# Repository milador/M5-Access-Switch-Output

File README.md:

# M5-Access-Switch-Output

A Wi-Fi enabled Adaptive Switch Output device based on ESP32 M5StickC/M5StickCPlus which offers up to two 3.5mm switch outputs. The M5 Switch Output can be used to operate up to two switch adapted devices.

## Requirements and setup instructions 
The setup process is divided to three main catagories:

  1. [Hardware](./Hardware/) : The required hardware and design files
  2. [Software](./Software/) : The required software
  3. [Documentation](./Documentation/) : The assembly guide,user guide and other documents 

## License

### MIT License

Copyright (c) 2022 milador

Permission is hereby granted, free of charge, to any person obtaining a copy of this software and associated documentation files (the "Software"), to deal in the Software without restriction, including without limitation the rights to use, copy, modify, merge, publish, distribute, sublicense, and/or sell copies of the Software, and to permit persons to whom the Software is furnished to do so, subject to the following conditions:

The above copyright notice and this permission notice shall be included in all copies or substantial portions of the Software.

THE SOFTWARE IS PROVIDED "AS IS", WITHOUT WARRANTY OF ANY KIND, EXPRESS OR IMPLIED, INCLUDING BUT NOT LIMITED TO THE WARRANTIES OF MERCHANTABILITY, FITNESS FOR A PARTICULAR PURPOSE AND NONINFRINGEMENT. IN NO EVENT SHALL THE AUTHORS OR COPYRIGHT HOLDERS BE LIABLE FOR ANY CLAIM, DAMAGES OR OTHER LIABILITY, WHETHER IN AN ACTION OF CONTRACT, TORT OR OTHERWISE, ARISING FROM, OUT OF OR IN CONNECTION WITH THE SOFTWARE OR THE USE OR OTHER DEALINGS IN THE SOFTWARE.

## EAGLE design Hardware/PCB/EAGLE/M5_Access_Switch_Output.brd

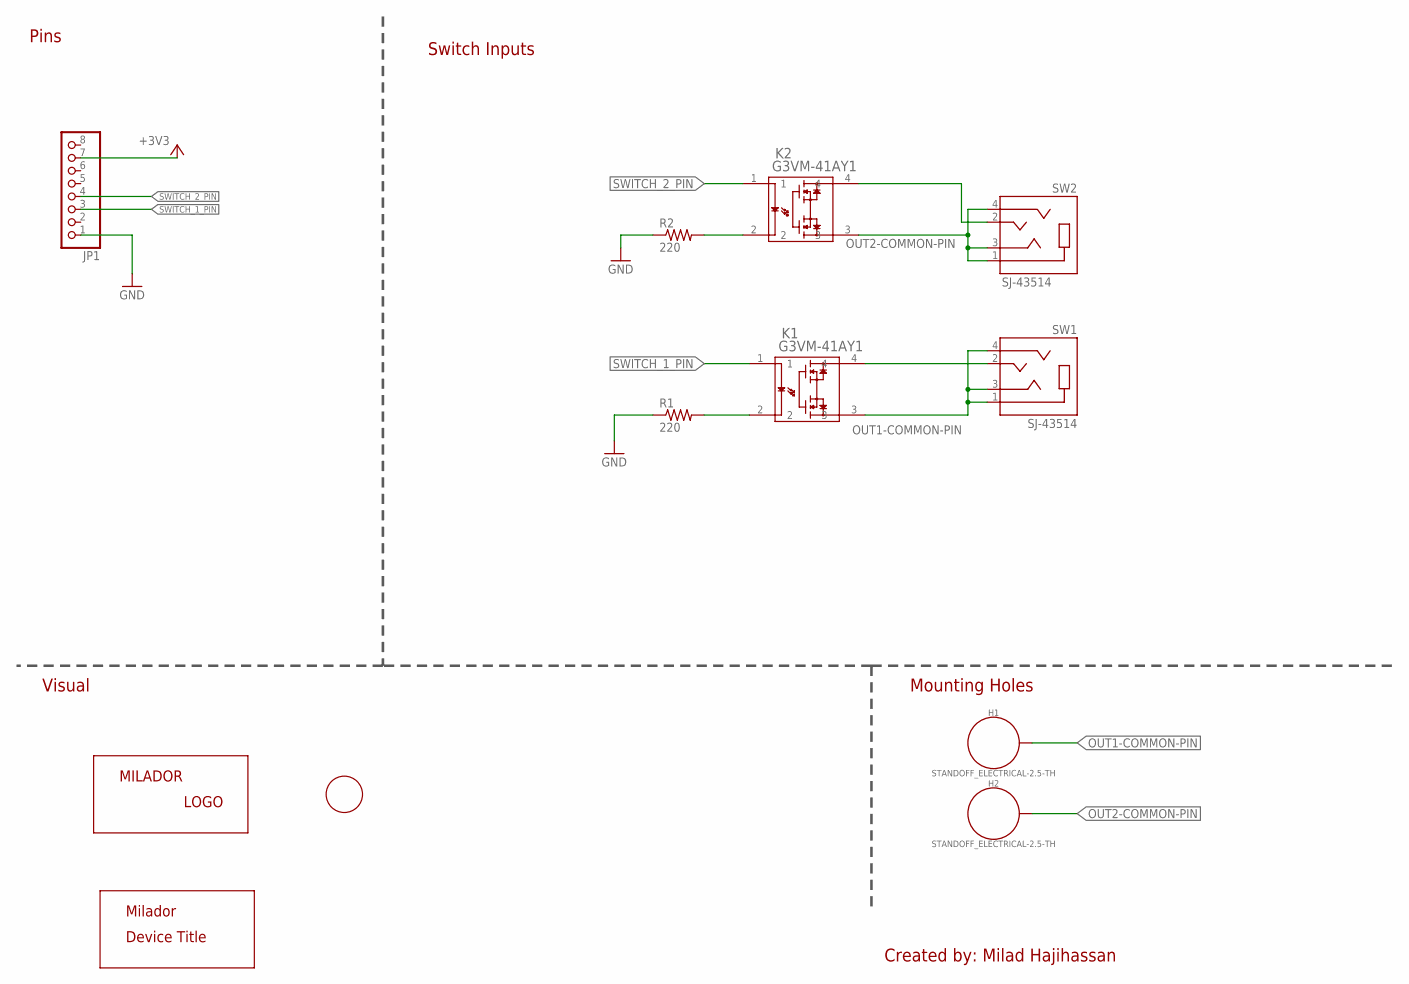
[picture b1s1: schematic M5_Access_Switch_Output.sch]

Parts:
H1, H2: STANDOFF_ELECTRICAL-2.5-TH; STANDOFF-ELECTRICAL-2.5-TH
JP1: HEADER_MALE-1X8ROUND-RA; 1X08_ROUND_RA
K1, K2: G3VM-41AY1; A-DIP4_THD_OMR
LABEL_DEVICE_TOP: MILADOR-DEVICE-M5-ACCESS-SWITCH; MILADOR_M5_ACCESS_SWITCH
LABEL_LOGO_TOP: MILADOR-LOGO-SM; MILADOR_LOGO2
LABEL_OUTPUT_TOP: MILADOR-SWITCH-NAME-SW-OUTPUT; SWITCH-OUTPUT
R1, R2: 220; RESISTOR_0204/5
SW1, SW2: SJ-43514; CUI_SJ-43514

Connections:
+3V3: JP1.7
GND: JP1.1, R1.1, R2.1
unnamed: K2.2, R2.2
unnamed: K1.2, R1.2
OUT1-COMMON-PIN: H1.P1, K1.3, SW1.1 (SLEEVE), SW1.3 (RING1), SW1.4 (RING2)
OUT2-COMMON-PIN: H2.P1, K2.3, SW2.1 (SLEEVE), SW2.3 (RING1), SW2.4 (RING2)
OUT-1-PIN: K2.4, SW2.2 (TIP)
OUT-2-PIN: K1.4, SW1.2 (TIP)
SWITCH_1_PIN: JP1.3, K1.1
SWITCH_2_PIN: JP1.4, K2.1

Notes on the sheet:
Switch Inputs
Pins
Mounting Holes
Visual
Created by: Milad Hajihassan

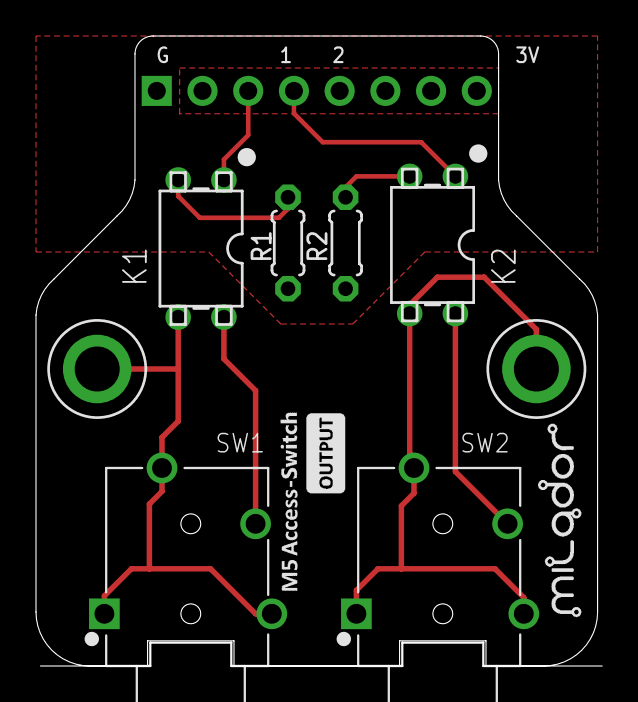
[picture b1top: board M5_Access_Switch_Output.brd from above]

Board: 2 copper layers, 31.2 x 35.0 mm, 12 parts (1 on the bottom side), 9 nets.

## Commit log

2022-08-20 Added Stereo jack design
2022-08-20 Updated design to two mono jack design
2022-08-20 Added basic software
2022-08-20 Added gerber files
2022-08-29 Added enclosure/case files
2022-08-29 Added BOM
2022-09-25 Updated Code
2022-10-01 Updated BOM file
2022-10-01 Updated the code
2022-10-01 Added assembly guide
2022-10-01 Added image
2022-10-01 Added user guide
2022-10-01 Updated code for M5StickCPlus
2022-10-01 Added M5StickC code
2022-10-10 Updated ssid
2022-10-10 Updated user manual

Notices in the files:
parts and their libraries:
COPYRIGHT: Copyright (C) 2022 Ultra Librarian. All rights reserved.
